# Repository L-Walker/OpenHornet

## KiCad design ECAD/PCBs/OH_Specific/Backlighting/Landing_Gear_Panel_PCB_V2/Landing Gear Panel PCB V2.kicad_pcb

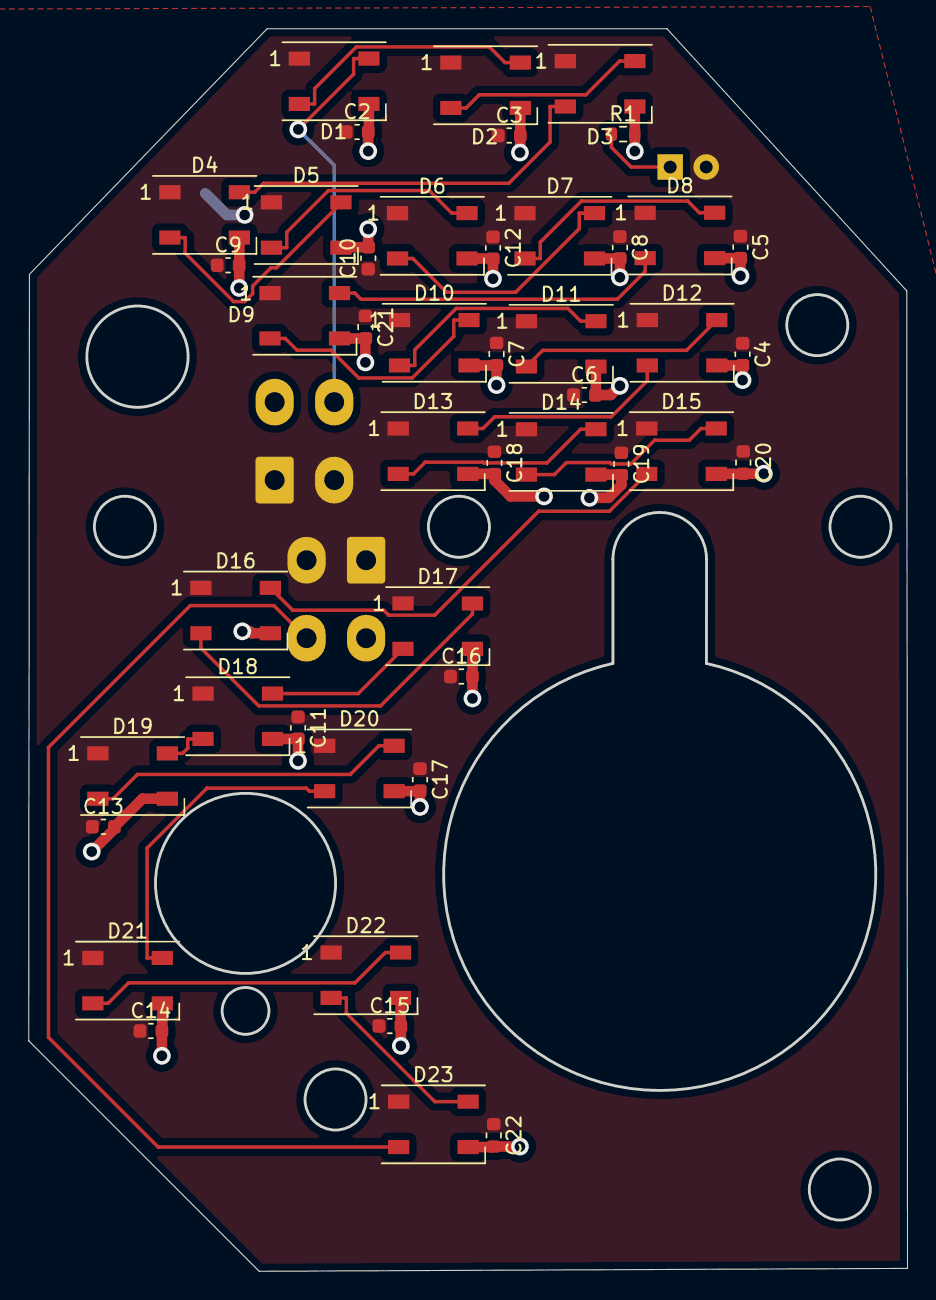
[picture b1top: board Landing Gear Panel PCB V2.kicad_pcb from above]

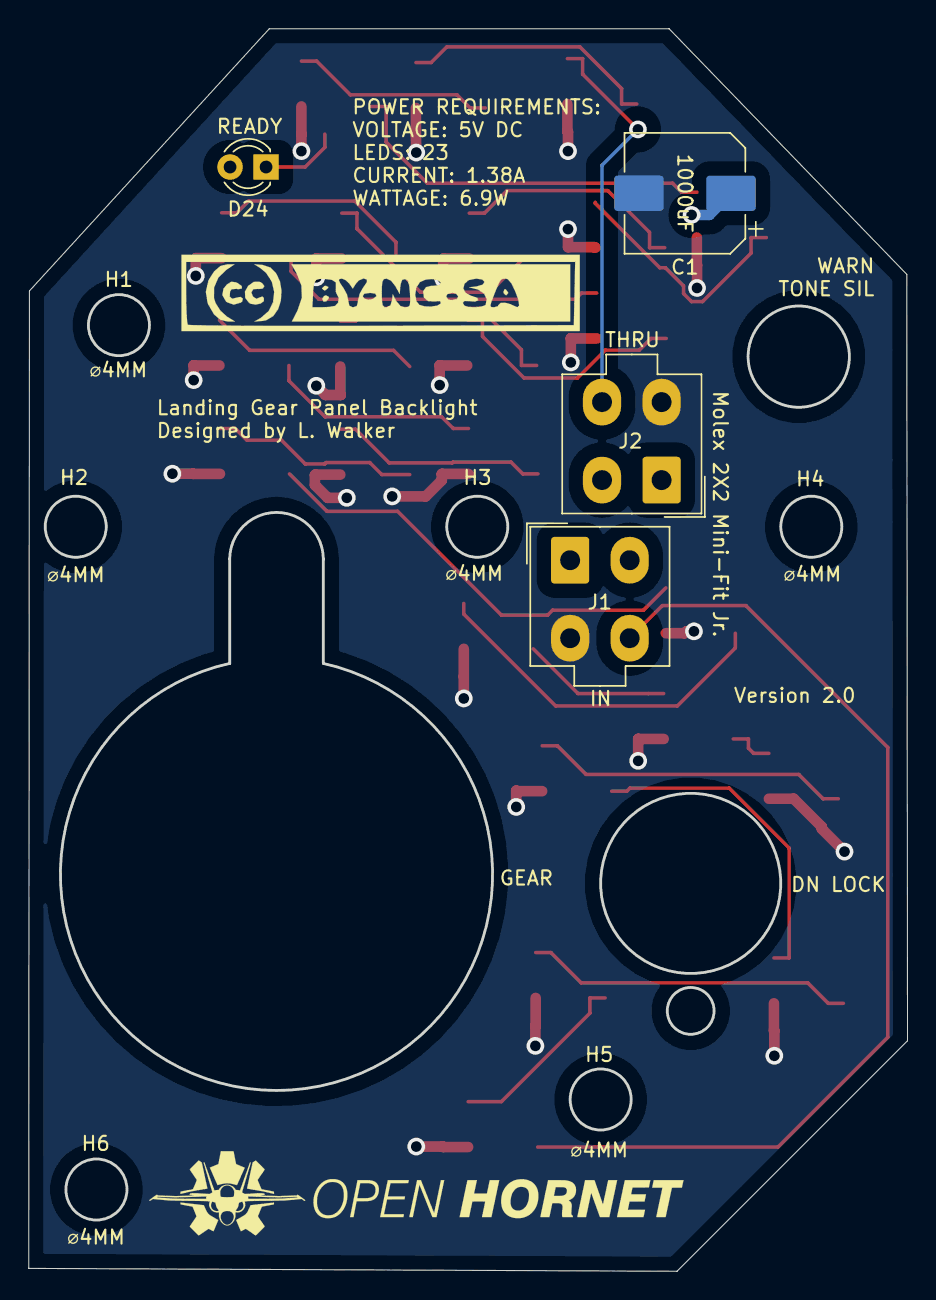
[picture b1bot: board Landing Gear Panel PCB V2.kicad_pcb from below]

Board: 2 copper layers, 62.0 x 87.6 mm, 49 parts (4 on the bottom side), 27 nets.

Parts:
C1: C_Polarized; CP_Elec_8x10
C2, C3, C4, C5, C6, C7, C8, C9, C10, C11, C12, C13, C14, C15, C16, C17, C18, C19, C20, C21, C22: C; C_0603_1608Metric
D1, D2, D3, D4, D5, D6, D7, D8, D9, D10, D11, D12, D13, D14, D15, D16, D17, D18, D19, D20, D21, D22, D23: WS2812B; LED_WS2812B_PLCC4_5.0x5.0mm_P3.2mm
D24: LED; LED_D3.0mm
J1, J2: Conn_01x04_Female; Molex_Mini-Fit_Jr_5566-04A_2x02_P4.20mm_Vertical
R1: R; R_0603_1608Metric

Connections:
/DATAIN: D1.4, J2.4
/DATAOUT: D23.2, J1.4
/LED+5V: C1.1, C2.1, C3.1, C4.1, C5.1, C6.1, C7.1, C8.1, C9.1, C10.1, C11.1, C12.1, C13.1, C14.1, C15.1, C16.1, C17.1, C18.1, C19.1, C20.1, C21.1, C22.1, D1.1, D2.1, D3.1, D4.1, D5.1, D6.1, D7.1, D8.1, D9.1, D10.1, D11.1, D12.1, D13.1, D14.1, D15.1, D16.1, D17.1, D18.1, D19.1, D20.1, D21.1, D22.1, D23.1, D24.2, J1.1, J1.2, J2.1, J2.2
/LEDGND: C1.2, C2.2, C3.2, C4.2, C5.2, C6.2, C7.2, C8.2, C9.2, C10.2, C11.2, C12.2, C13.2, C14.2, C15.2, C16.2, C17.2, C18.2, C19.2, C20.2, C21.2, C22.2, D1.3, D2.3, D3.3, D4.3, D5.3, D6.3, D7.3, D8.3, D9.3, D10.3, D11.3, D12.3, D13.3, D14.3, D15.3, D16.3, D17.3, D18.3, D19.3, D20.3, D21.3, D22.3, D23.3, J1.3, J2.3, R1.2
unnamed: D1.2, D2.4
unnamed: D2.2, D3.4
unnamed: D3.2, D4.4
unnamed: D4.2, D5.4
unnamed: D5.2, D6.4
unnamed: D6.2, D7.4
unnamed: D7.2, D8.4
unnamed: D8.2, D9.4
unnamed: D10.2, D11.4
unnamed: D9.2, D10.4
unnamed: D11.2, D12.4
unnamed: D12.2, D13.4
unnamed: D13.2, D14.4
unnamed: D14.2, D15.4
unnamed: D15.2, D16.4
unnamed: D16.2, D17.4
unnamed: D17.2, D18.4
unnamed: D18.2, D19.4
unnamed: D19.2, D20.4
unnamed: D20.2, D21.4
unnamed: D21.2, D22.4
unnamed: D22.2, D23.4
unnamed: D24.1, R1.1

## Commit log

2020-11-15 Update MS21385-04ENN v3.sldprt
    Addition of indica for the knob.
2021-01-04 Version 2 Backlighting PCBs
    Changes:
    - Using Mini-Fit Jr 2x2 Connectors.
    - +5v Top Plane, solid copper fill.
    - GND Back Plane, solid copper fill.
    - Added filter caps to ~90% of the LEDs for noise/voltage spike supression.
    - Added all OH Silkscreening
